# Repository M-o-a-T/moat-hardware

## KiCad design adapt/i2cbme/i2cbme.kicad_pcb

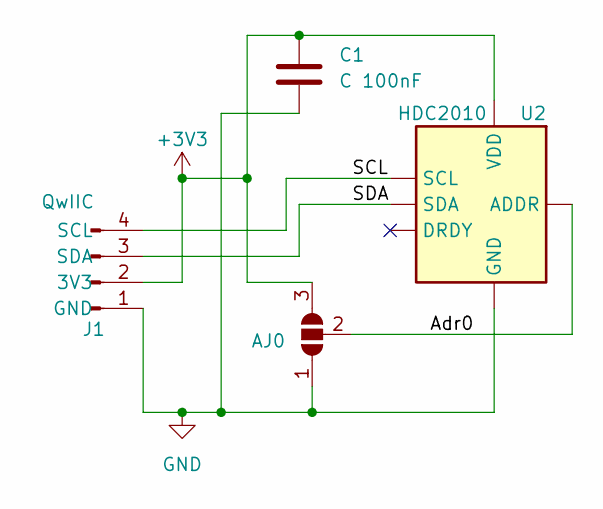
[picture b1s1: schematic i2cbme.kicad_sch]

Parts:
AJ0: SolderJumper_3_Open; SolderJumper-3_P2.0mm_Open_TrianglePad1.0x1.5mm
C1: C 100nF; C_0402_1005Metric; LCSC C22435938
J1: QwIIC; JST_SH_SM04B-SRSS-TB_1x04-1MP_P1.00mm_Horizontal; LCSC C160404
U2: HDC2010; Texas_DSBGA HDC2010; LCSC C477922

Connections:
+3V3: AJ0.3 (B), C1.1, J1.2 (3V3), U2.A1 (VDD)
/Adr0: AJ0.2 (C), U2.B1 (ADDR)
/SCL: J1.4 (SCL), U2.B2 (SCL)
/SDA: J1.3 (SDA), U2.A2 (SDA)
GND: AJ0.1 (A), C1.2, J1.1 (GND), U2.C1 (GND)

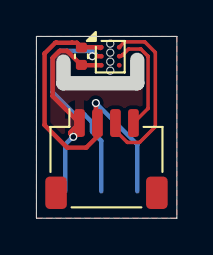
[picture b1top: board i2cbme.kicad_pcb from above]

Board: 2 copper layers, 7.8 x 10.1 mm, 4 parts (1 on the bottom side), 5 nets.

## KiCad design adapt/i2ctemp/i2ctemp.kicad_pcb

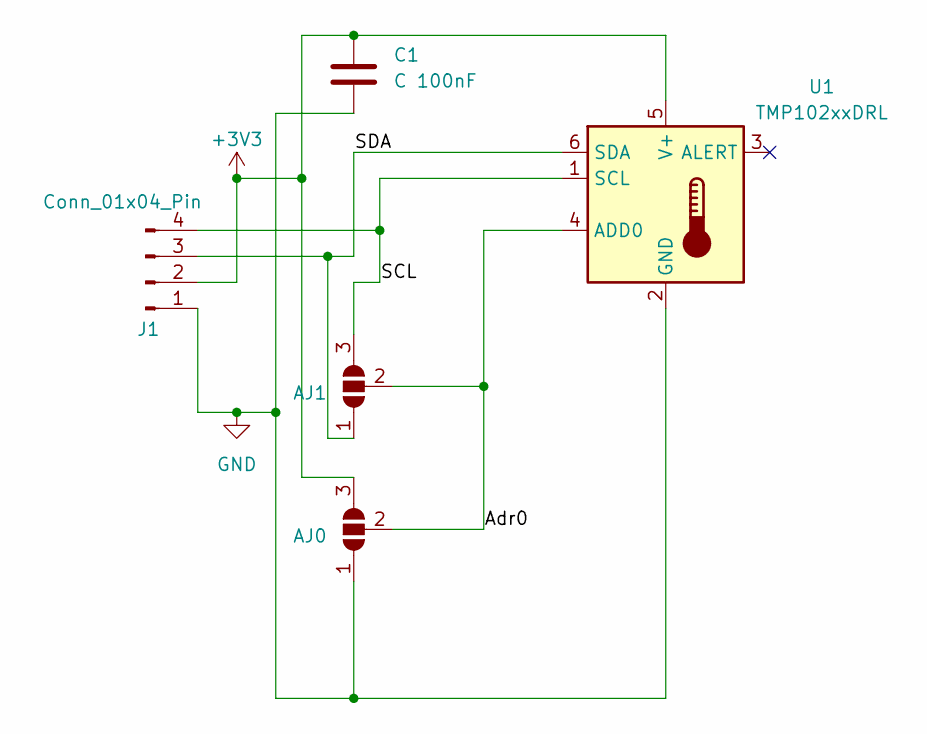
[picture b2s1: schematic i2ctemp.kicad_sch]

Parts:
AJ0, AJ1: SolderJumper_3_Open
C1: C 100nF; C_0402_1005Metric; LCSC C22435938
J1: Conn_01x04_Pin; JST_SH_SM04B-SRSS-TB_1x04-1MP_P1.00mm_Horizontal; LCSC C160404
U1: TMP102xxDRL; SOT-563; LCSC C5692997

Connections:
+3V3: AJ0.3 (B), C1.1, J1.2, U1.5 (V+)
/Adr0: AJ0.2 (C), AJ1.2 (C), U1.4 (ADD0)
/SCL: AJ1.3 (B), J1.4, U1.1 (SCL)
/SDA: AJ1.1 (A), J1.3, U1.6 (SDA)
GND: AJ0.1 (A), C1.2, J1.1, U1.2 (GND)

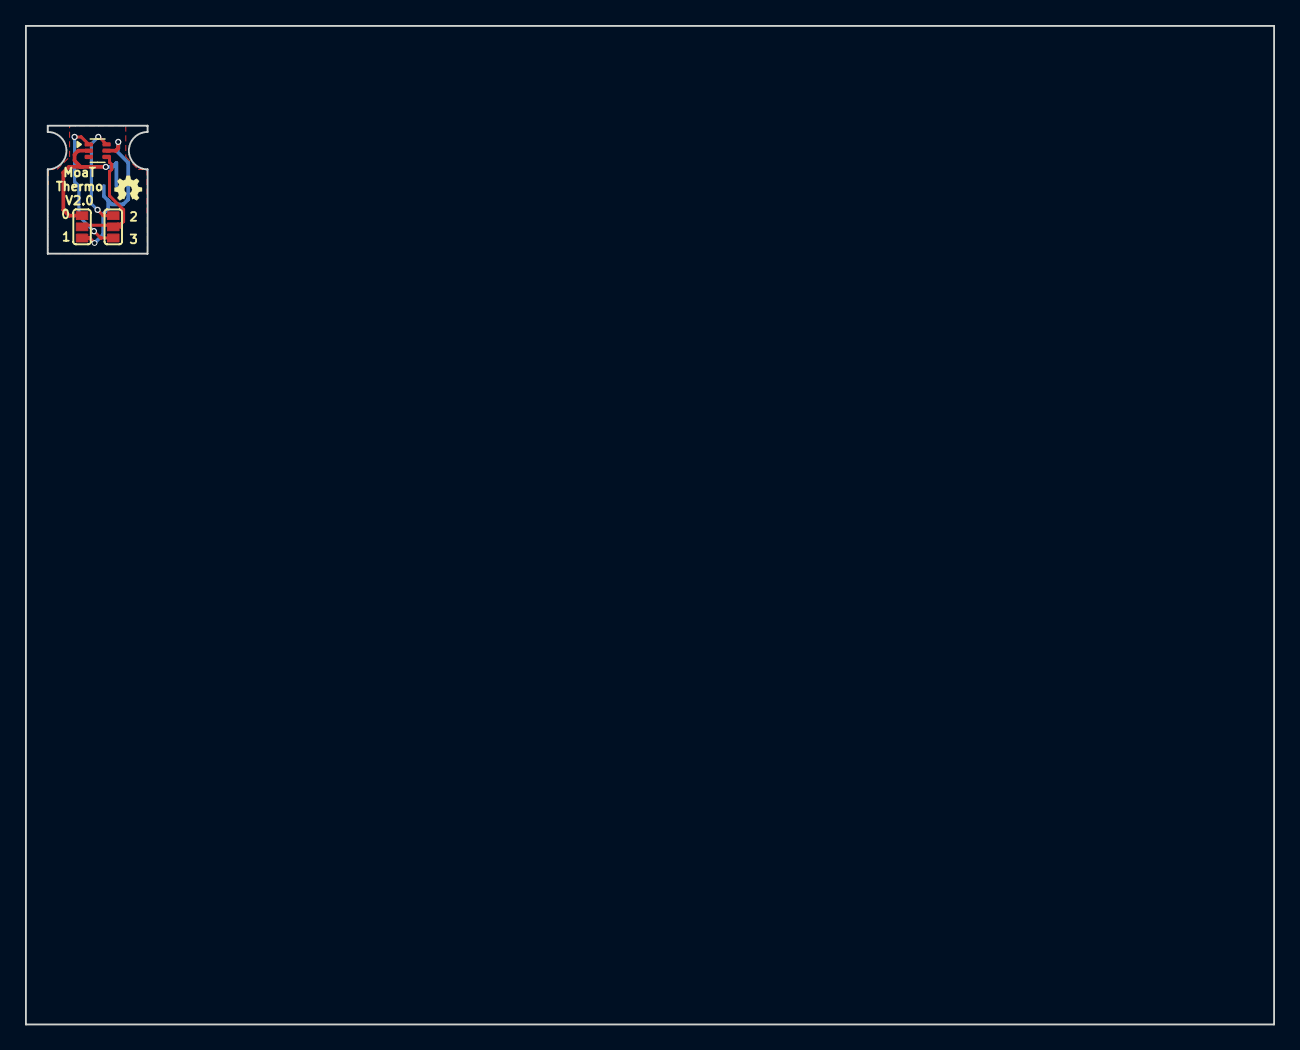
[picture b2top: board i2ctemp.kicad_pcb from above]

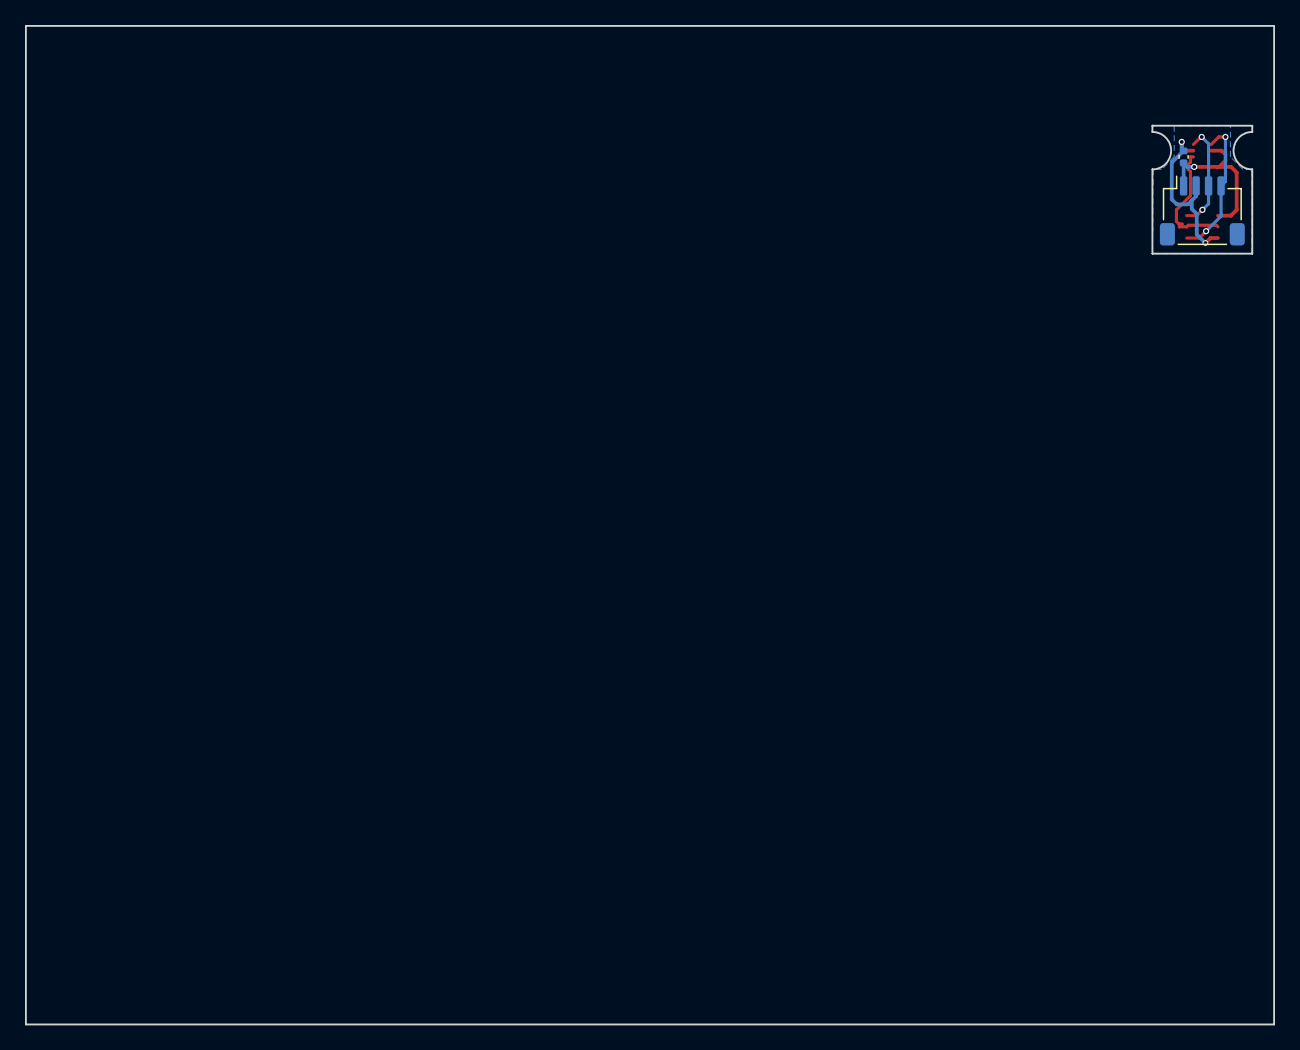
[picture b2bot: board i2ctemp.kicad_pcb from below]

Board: 2 copper layers, 100.0 x 80.0 mm, 5 parts (2 on the bottom side), 5 nets.

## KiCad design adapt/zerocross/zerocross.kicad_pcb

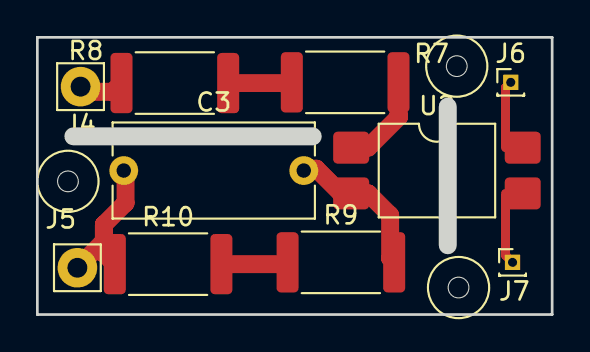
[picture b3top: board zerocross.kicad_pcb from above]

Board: 2 copper layers, 28.6 x 15.4 mm, 10 parts (0 on the bottom side), 8 nets.

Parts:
C3: 22nF 400V X2; C_Rect_L11.0mm_W5.1mm_P10.00mm_MKT
J4, J5: Conn_01x01_Pin; Pin_D1.1mm_L8.5mm_W2.5mm_FlatFork
J6, J7: Conn_01x01_Pin; PinHeader_1x01_P1.00mm_Vertical
R7, R8: 2k2; R_2512_6332Metric
R9, R10: 470 100V; R_2512_6332Metric
U2: PC814; SMDIP-4_W9.53mm

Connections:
/GND: J7.1, U2.3
/L: C3.1, J5.1, R10.1
/N: J4.1, R8.1
unnamed: C3.2, R9.2, U2.2
unnamed: J6.1, U2.4
unnamed: R7.1, R8.2
unnamed: R7.2, U2.1
unnamed: R9.1, R10.2

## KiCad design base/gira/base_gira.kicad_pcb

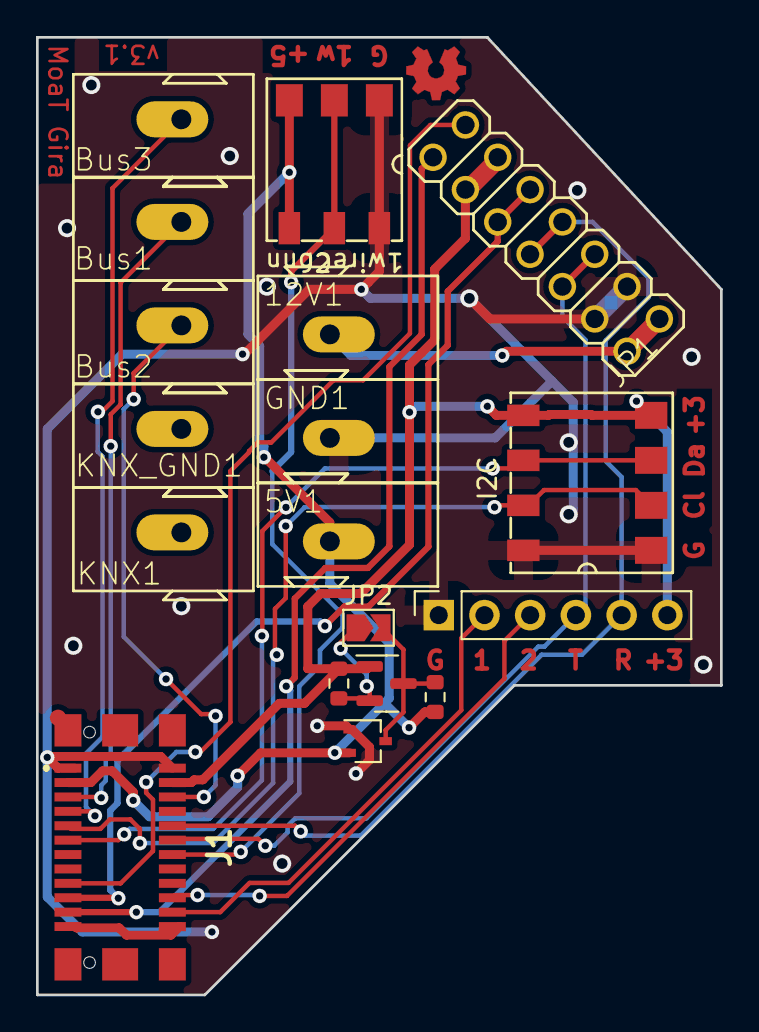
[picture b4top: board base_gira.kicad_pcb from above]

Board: 2 copper layers, 38.0 x 53.2 mm, 18 parts (0 on the bottom side), 20 nets.

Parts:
5V1, 12V1: WAGO_243; Wago_Terminal_243
Bus1, Bus2, Bus3: WAGO_243; Wago_Terminal_243
D1: BAT54SW; SOT-323_SC-70
GND1: WAGO_243; Wago_Terminal_243
J1: Moat_Bus_wire; TE_1775014_socket
J2: 1wireConn; AVX_9276_3Pin
J3: I2C; AVX_9276_4Pin
J4: Conn_01x06; PinSocket_1x06_P2.54mm_Vertical
JP1: Gira; 2X07
JP2: SolderJumper_2_Open; SolderJumper-2_P1.3mm_Open_TrianglePad1.0x1.5mm
KNX1: WAGO_243; Wago_Terminal_243
KNX_GND1: WAGO_243; Wago_Terminal_243
Q1: 2N7002; SOT-23
R1, R2: 10k; R_0603_1608Metric

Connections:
+3V3: J1.4 (3V3), J3.4, J4.6, JP1.11, JP1.12, Q1.1 (G), R1.1
+5V: 5V1.1, D1.2, J1.3 (5V), J2.3 (+5V), R2.1
+12V: 12V1.1, JP1.1, JP1.2
/1wire: J1.14 (1W), J2.2 (1wire)
/1wire_3: JP2.1 (A), Q1.2 (S), R1.2
/1wire_5: D1.3, JP2.2 (B), Q1.3 (D), R2.2
/RxD: J1.10 (Rx), J4.5, JP1.7, JP1.8
/SCL: J1.9 (Clk), J3.2
/SDA: J1.11 (Dat), J3.3
/T1: J1.22 (T1), J4.2
/T2: J1.20 (T2), J4.3
/TEST: J1.21 (S1), JP1.14
/TxD: J1.12 (Tx), J4.4, JP1.5, JP1.6
/Unk_1: J1.19 (S2), JP1.9, JP1.10
/Unk_2: J1.17 (S3), JP1.13
GND: D1.1, GND1.1, J1.1 (GND), J1.2 (GND), J2.1 (GND), J3.1, J4.1, JP1.3, JP1.4
GNDPWR: J1.23 (GND), J1.24 (GND)
unnamed: Bus1.1, J1.5 (Bus_1)
unnamed: Bus2.1, J1.6 (Bus_2)
unnamed: Bus3.1, J1.7 (Bus_3)

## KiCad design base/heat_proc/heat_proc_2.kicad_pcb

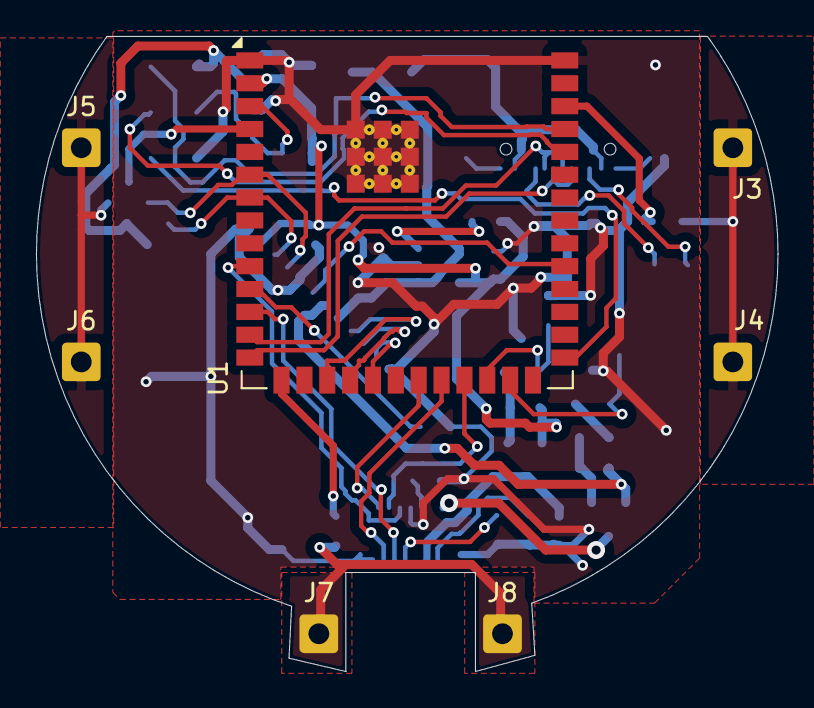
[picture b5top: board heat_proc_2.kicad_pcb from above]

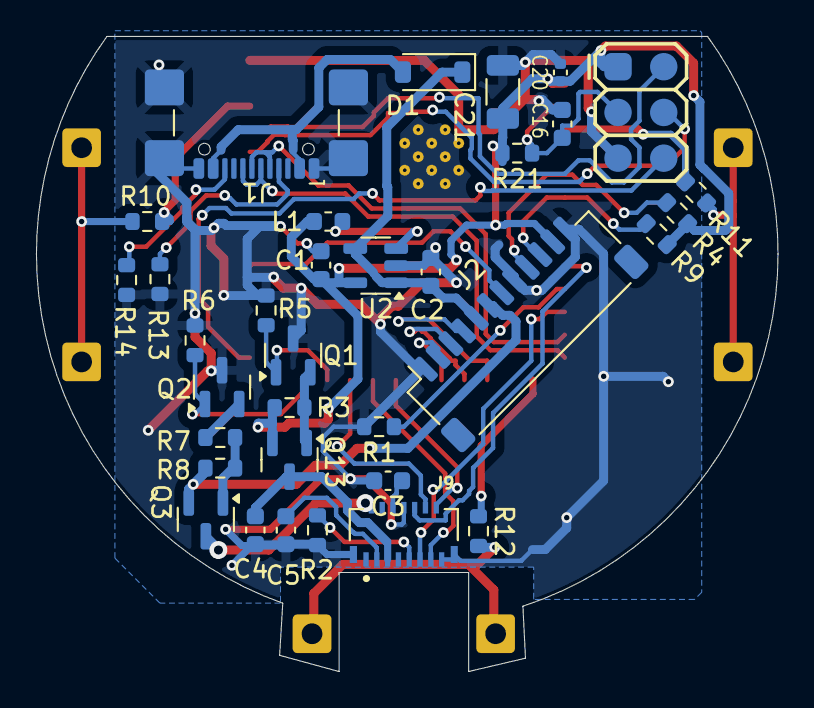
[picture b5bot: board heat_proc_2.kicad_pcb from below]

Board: 2 copper layers, 41.2 x 35.3 mm, 41 parts (34 on the bottom side), 42 nets.

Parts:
C1, C2: CP_10µ_16V_0603; C_0603_1608Metric
C3, C4: C_1µ_25V_0603; C_0603_1608Metric
C5: 4.7µF 25V; C_0603_1608Metric
C16: 10nF; C_0603_1608Metric
C20: 100nF; C_0402_1005Metric
C21: 22µF; C_1206_3216Metric
D1: MBR1020VL; D_SOD-123
J1: USB_C_Receptacle; USB_C_Receptacle_GCT_USB4110
J2: Moat_Heat_12; JST_SH_SM12B-SRSS-TB_1x12-1MP_P1.00mm_Horizontal
J3, J4, J5, J6, J7, J8: Conn_01x01_Socket; SolderWire-0.5sqmm_1x01_D0.9mm_OD2.1mm
J9: 1-2328724-5; TE_1-2328724-5
L1: 4.7 µH; L_0603_1608Metric
Prog1: PogoPad; 2X3_PAD
Q1, Q2: HX2302A; SOT-23
Q3, Q13: HX2301V; SOT-23
R1, R3, R5, R6, R8: R_100k_0603; R_0603_1608Metric
R2: 510k; R_0603_1608Metric
R4, R9: R_1k_0603; R_0603_1608Metric
R7: R_220k_0603; R_0603_1608Metric
R10, R11, R12: 510; R_0603_1608Metric
R13, R14: 5.1k; R_0603_1608Metric
R21: 10k; R_0603_1608Metric
U1: ESP32-S3-WROOM-2
U2: HX1001; TSOT-23-5

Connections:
+3.3V: C1.1, C20.1, C21.1, J2.11 (3v3), L1.2, Prog1.1 (+3V), Q13.2 (S), R3.2, R4.2, R9.2, R21.2, U1.2 (3V3), U2.5 (Vout)
+5V: C2.1, D1.1 (K), J2.5 (5V), U2.1 (EN), U2.4 (Vin)
+12V: J2.6 (12V), Q3.2 (S), R8.2
/Boot: Prog1.6 (Boot0), U1.27 (IO0)
/Bus1: J2.2 (Bus1), U1.19 (IO11)
/Bus2: J2.3 (Bus2), U1.18 (IO10)
/Bus3: J2.4 (Bus3), U1.17 (IO9)
/D_Reset: J9.11 (RESET), U1.12 (IO8)
/EN: C16.1, Prog1.3 (Reset), R21.1, U1.3 (EN)
/ISCL: J2.9 (SCL), R4.1, U1.6 (IO6)
/ISDA: J2.10 (SDA), R9.1, U1.7 (IO7)
/MISO: R1.1, U1.11 (IO18)
/MOSI: J9.14 (SDIN), U1.21 (IO13)
/P3.3: C4.1, J9.5 (VCI), Q13.3 (D)
/P12: J9.2 (VCC), Q3.3 (D)
/PWR3: Q1.1 (G), R5.2, U1.24 (IO47)
/PWR12: Q2.1 (G), R6.2, U1.25 (IO48)
/Rx: Prog1.4 (Rx), U1.36 (RXD0/IO44)
/SCK: J9.13 (SCLK), U1.22 (IO14)
/SCS: J9.10 (CS), U1.10 (IO17)
/SDC: J9.12 (DC), U1.23 (IO21)
/Sw24: J2.7 (Sw24), U1.31 (IO38)
/TPbottom: J7.1, J8.1, R12.2
/TPleft: J5.1, J6.1, R11.2
/TPright: J3.1, J4.1, R10.2
/Tbottom: R12.1, U1.15 (IO3)
/Tleft: R11.1, U1.4 (IO4)
/Tright: R10.1, U1.38 (IO2)
/Tx: Prog1.2 (Tx), U1.37 (TXD0/IO43)
/USB+: J1.A6 (D+), J1.B6 (D+), U1.14 (USB_D+/IO20)
/USB-: J1.A7 (D-), J1.B7 (D-), U1.13 (USB_D-/IO19)
GND: C1.2, C2.2, C3.2, C4.2, C5.2, C16.2, C20.2, C21.2, J1.A1 (GND), J1.A12 (GND), J1.B1 (GND), J1.B12 (GND), J1.S1 (SHIELD), J2.1 (GND), J2.8 (GND), J2.12 (GND), J9.8 (VSS), J9.15 (VLSS), J9.S1 (SHIELD), J9.S2 (SHIELD), Prog1.5 (GND), Q1.3 (S), Q2.3 (S), R1.2, R2.2, R5.1, R6.1, R13.2, R14.2, U1.1 (GND), U1.40 (GND), U1.41 (GND), U2.2 (GND)
unnamed: D1.2 (A), J1.A4 (VBUS), J1.A9 (VBUS), J1.B4 (VBUS), J1.B9 (VBUS)
unnamed: J1.A5 (CC1), R13.1
unnamed: J1.B5 (CC2), R14.1
unnamed: J9.9 (IRef), R2.1
unnamed: C3.1, J9.6 (VCAP)
unnamed: C5.1, J9.3 (VCOMH)
unnamed: Q1.2 (D), Q13.1 (G), R3.1
unnamed: Q2.2 (D), R7.1
unnamed: Q3.1 (G), R7.2, R8.1
unnamed: L1.1, U2.3 (SW)

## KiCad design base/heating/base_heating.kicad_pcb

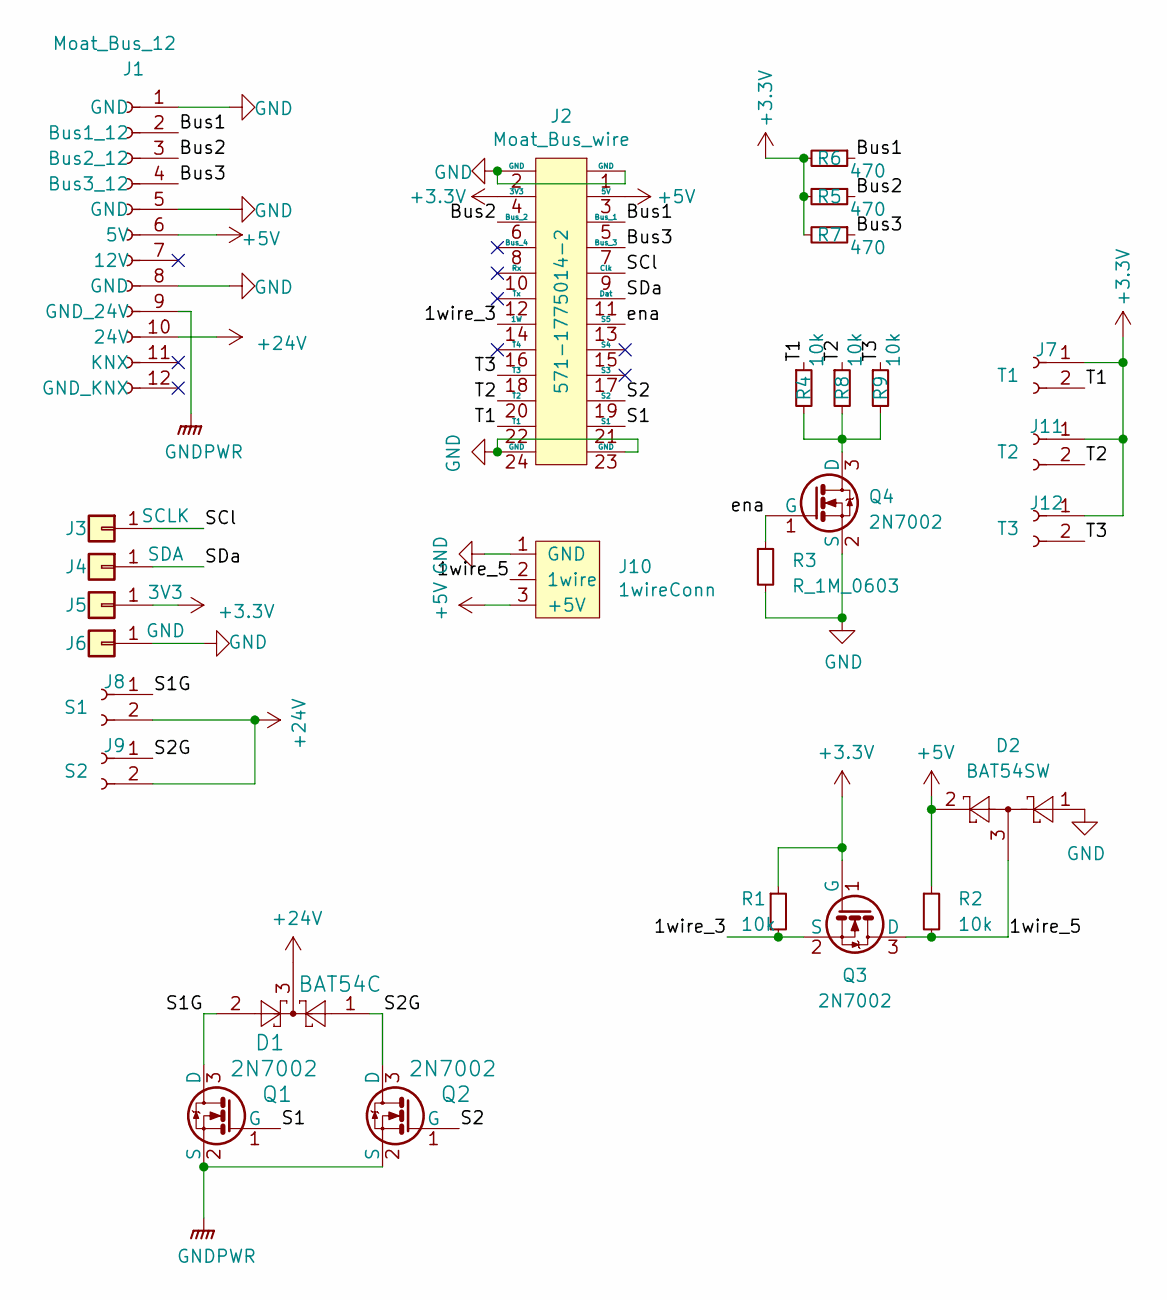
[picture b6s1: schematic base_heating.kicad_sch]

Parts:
D1: BAT54C; SOT-23
D2: BAT54SW; SOT-323_SC-70
J1: Moat_Bus_12; MoaT_12_Pin_V; MfgrPart GBEC202-0679B001C1AF
J2: Moat_Bus_wire; TE_1775014_socket; Digikey A118067CT-ND
J3: SCLK; Wago_Terminal_243
J4: SDA; Wago_Terminal_243
J5: 3V3; Wago_Terminal_243
J6: GND; Wago_Terminal_243
J7: T1; 1X02_GN
J8: S1; 1X02_GN
J9: S2; 1X02_GN
J10: 1wireConn; AVX_9276_3Pin
J11: T2; 1X02_GN
J12: T3; 1X02_GN
Q1, Q2: 2N7002; SOT23
Q3, Q4: 2N7002; SOT-23
R1, R2: 10k; R_0603_1608Metric
R3: R_1M_0603; R_0603_1608Metric; LCSC C328340
R4, R8, R9: 10k; R_0603_1608Metric; LCSC C25804
R5, R6, R7: 470; R_0603_1608Metric

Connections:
+3V3: J2.4 (3V3), J5.1, J7.1, J11.1, J12.1, Q3.1 (G), R1.1, R5.2, R6.2, R7.2
+5V: D2.2, J1.6 (5V), J2.3 (5V), J10.3 (+5V), R2.1
+24V: D1.3, J1.10 (24V), J8.2, J9.2
/1wire_3: J2.14 (1W), Q3.2 (S), R1.2
/1wire_5: D2.3, J10.2 (1wire), Q3.3 (D), R2.2
/Bus1: J1.2 (Bus1_12), J2.5 (Bus_1), R6.1
/Bus2: J1.3 (Bus2_12), J2.6 (Bus_2), R7.1
/Bus3: J1.4 (Bus3_12), J2.7 (Bus_3), R5.1
/S1: J2.21 (S1), Q1.1 (G)
/S1G: D1.2, J8.1, Q1.3 (D)
/S2: J2.19 (S2), Q2.1 (G)
/S2G: D1.1, J9.1, Q2.3 (D)
/SCl: J2.9 (Clk), J3.1
/SDa: J2.11 (Dat), J4.1
/T1: J2.22 (T1), J7.2, R4.1
/T2: J2.20 (T2), J11.2, R8.1
/T3: J2.18 (T3), J12.2, R9.1
/ena: J2.13 (S5), Q4.1 (G), R3.1
GND: D2.1, J1.1 (GND), J1.5 (GND), J1.8 (GND), J2.1 (GND), J2.2 (GND), J2.23 (GND), J2.24 (GND), J6.1, J10.1 (GND), Q4.2 (S), R3.2
GNDPWR: J1.9 (GND_24V), Q1.2 (S), Q2.2 (S)
unnamed: Q4.3 (D), R4.2, R8.2, R9.2

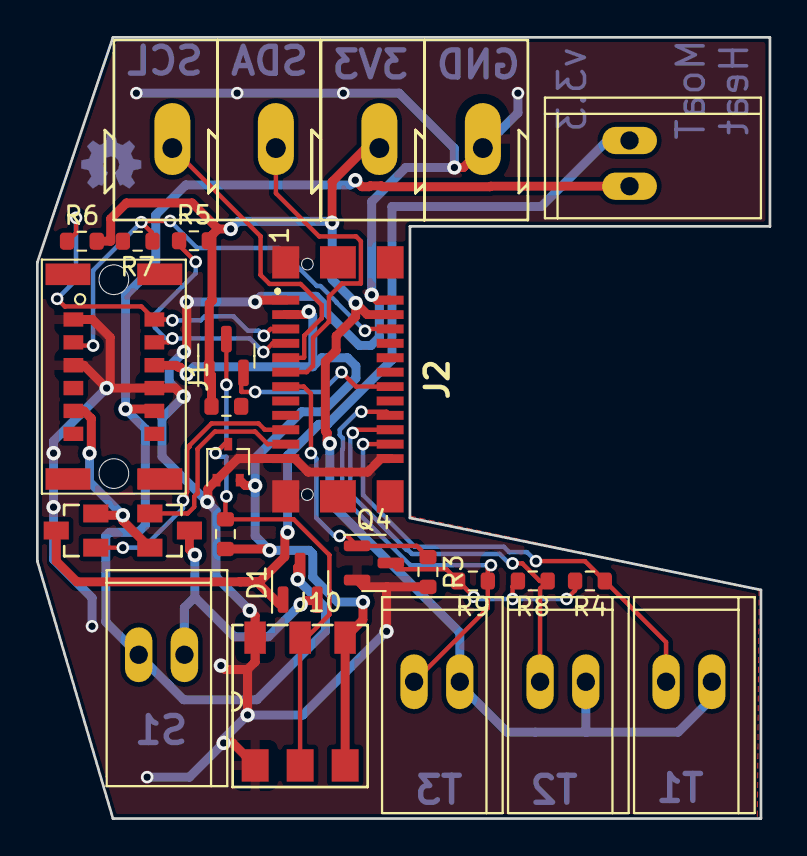
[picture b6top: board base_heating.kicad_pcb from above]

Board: 2 copper layers, 40.7 x 43.4 mm, 27 parts (0 on the bottom side), 21 nets.
